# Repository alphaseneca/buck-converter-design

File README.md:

# buck-converter-design

This project focuses on the design and implementation of a **synchronous buck converter**, aiming for improved efficiency and reduced output ripple suitable for sensitive applications. The key aspect of the design is the careful selection of the **buck converter IC**, which plays a pivotal role in defining the overall performance, efficiency, and practicality of the system. Given the wide variety of ICs available, the process required in-depth research, tradeoff analysis, and simulation to select the most appropriate component.

## Introduction

A **buck converter** is a widely used DC-DC converter topology known for its simplicity and efficiency in stepping down voltage levels. However, the performance of a buck converter heavily depends on the **IC selected**, which determines parameters like efficiency, output ripple, switching frequency, and current handling capability.

In the early stages of this project, I explored various commercially available buck converter ICs. I started by reviewing the datasheet of the **LM2596-5V**, a commonly found and affordable buck converter IC used in general-purpose circuits. However, during the datasheet study, I realized that the LM2596 operates in **non-synchronous mode**, which uses an external diode in the freewheeling phase. This leads to higher losses, especially at lower output voltages or higher currents. And is also expensive.

Further research introduced me to the **synchronous buck converter topology**, where the freewheeling diode is replaced by a low-side MOSFET. This approach significantly improves efficiency by reducing diode losses, making it suitable for modern, high-performance applications where efficiency and thermal management are critical.

To assist in the selection process, I utilized **Texas Instruments' WEBENCH Designer**, an online tool that helps engineers simulate and optimize power supply designs based on their requirements. Using this tool, I evaluated various TI synchronous buck converter ICs, comparing parameters like efficiency, output current capability, switching frequency, and thermal performance.

## Theoretical Background

A **synchronous buck converter** is a type of step-down converter that replaces the freewheeling diode with a **low-side MOSFET**. It operates with two MOSFETs (high-side and low-side) and a PWM controller that ensures precise switching and dead-time management.

https://resources.pcb.cadence.com/blog/synchronous-vs-nonsynchronous-dc-dc-conversion

### How It Works:

- When the **high-side MOSFET** is ON, current flows from input → inductor → load → ground.
- When it's OFF, the **low-side MOSFET** turns ON and allows the inductor to continue supplying current (instead of using a diode).
- The **inductor** stores energy during the ON phase and releases it during the OFF phase, smoothing current.
- The **capacitor** filters voltage ripple and stabilizes output.

---

## Design Requirements

- Input Voltage Range: 10-14 VDC
- Output Voltage: 5V
- Output Continuous Current: 3A
- Switching Frequency: 600kHz
- Ripple Limits: \***\*2–3% of Vout i.e **0.02\*5 = 10mV\*\*
  [ Consumer / FCC Class B as per FCC Part 15 ]

### Components Selection

- Buck Converter IC:
  Used **TPS564257** because it supports a wide input range from 3V to 17V, which covers my system’s required 10V to 14V input. Its built-in enable threshold can be configured using external resistors to ensure the system only turns on when the input is above 10V, protecting against undervoltage. The converter also offers efficient performance at up to 4A output and includes safety features like overcurrent and thermal shutdown, making it a safe and compact solution for my power supply design.
- Inductor Value:
  Target inductor ripple current: **20% to 50% of output current (IOUT)**
  Use this to calculate **inductor value using the standard formula:**

$$
\Delta I_L = \frac{(V_{IN} - V_{OUT}) \times V_{OUT}}{V_{IN} \times L \times f_{SW}}
$$

$$
I_{L(PEAK)} = I_{OUT} + \frac{\Delta I_L}{2}
$$

And According to the datasheet the recommended Inductor Value is 4.7uH and calculating the current rating we came to know that the inductor should be able to handle around **4.2A.**

- Capacitor Value: The output capacitor value are also recommended in the datasheet as:
  $Cout$ ⇒ 44uF. And it should be able to handle the current as the following equation suggests and should have low ESR.
  And the input capacitor are $Cin$ = 10uF and an additional 100nF for high frequency filtering. And the Voltage rating should be greater than the Input Voltage range.

$$
I_{CO(RMS)} = \frac{V_{OUT} \times (V_{IN} - V_{OUT})}{\sqrt{12} \times V_{IN} \times L \times f_{SW}}
$$

### Output Voltage Calculation:

The output voltage is set by the help of voltage divider arrangement of the Rfbt and Rfbb resistors. The recommended Rfbt is 200kohm and Rfbb is 30kohm for setting the output to 5V. And for the voltage other than that we can set using this formula:

$$
V_{OUT} = 0.6V \times \left(1 + \frac{R_{FBT}}{R_{FBB}}\right)
$$

The datasheet recommends using 1% tolerance resistors and to improve efficiency at very light loads, consider using larger value resistors.

### UVLO (Under Voltage Lock Out)

The EN pin accepts the voltage from and using a series of resistors Rent and Renb the converter is only turned on when the input voltage is higher than 10V

**_Calculation for EN divider to turn ON at 10V:_**

$$
V_{EN} = V_{IN} \times \frac{RENB}{REN + RENB}
$$

$$
REN = RENB \times \left(\frac{V_{IN(ON)}}{V_{EN}} - 1\right)
$$

The $Ven$ is 1.19V and the $Renb$ should be in k ohm range and thus setting the $Renb$ ⇒ 30kohm will give $Ren$ ⇒ 210kohm.

### Reliability and Over Voltage Protection:

For adding the reliability of the buck converter and also to limit the upper voltage to around 14 V we added a TVS diode in parallel to to the input supply. The TVS diode is **PTVS12VZ1USK** to be exact.

### Circuit Design:

### PCB:

---

### Simulation:

Simulation of the circuit is done using **WEBENCH Power Designer**.

- [Startup Simulation](./Simulations/WBDesign_Startup-1.pdf)
- [Load Transient Simulation](./Simulations/WBDesign_Load%20Transient-2.pdf)
- [Input Transient Simulation](./Simulations/WBDesign_Input%20Transient-3.pdf)
- [Steady State Simulation](./Simulations/WBDesign_Steady%20State-4.pdf)

### References:

- [TI TPS564257 Buck Converter Datasheet](https://www.ti.com/lit/ds/symlink/tps564257.pdf)
- [WEBENCH Power Designer](https://webench.ti.com/power-designer/)

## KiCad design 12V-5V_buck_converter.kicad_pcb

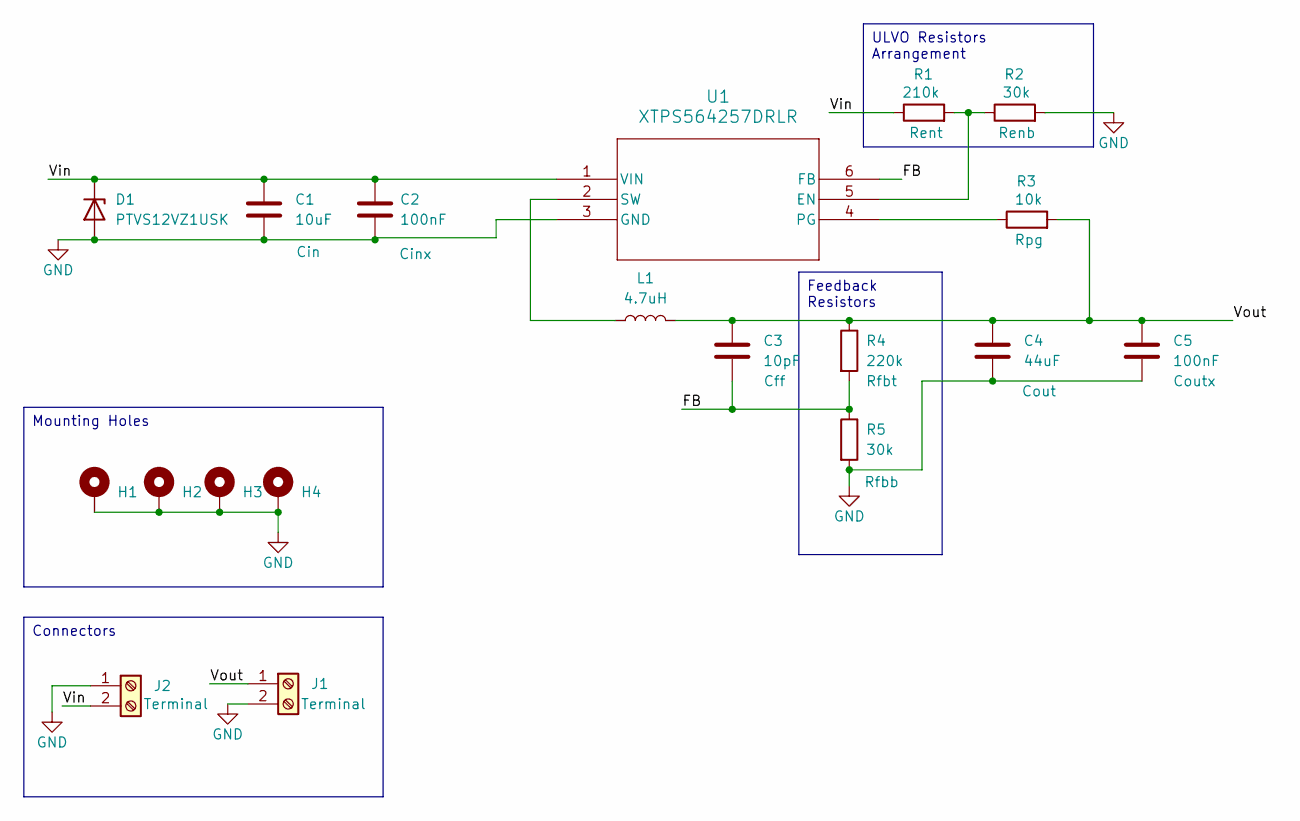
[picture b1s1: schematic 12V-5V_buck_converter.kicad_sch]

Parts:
C1: 10uF; C_0805_2012Metric
C2, C5: 100nF; C_0603_1608Metric
C3: 10pF; C_0402_1005Metric
C4: 44uF; C_0805_2012Metric
D1: PTVS12VZ1USK; Nexperia_DSN1608-2_1.6x0.8mm
H1, H2, H3, H4: MountingHole_Pad; MountingHole_2.2mm_M2_DIN965_Pad_TopBottom
J1, J2: Terminal; TerminalBlock_Phoenix_MPT-0,5-2-2.54_1x02_P2.54mm_Horizontal
L1: 4.7uH; IND_CLF10040T-4R7N-D
R1: 210k; R_0603_1608Metric
R2, R5: 30k; R_0603_1608Metric
R3: 10k; R_0603_1608Metric
R4: 220k; R_0603_1608Metric
U1: XTPS564257DRLR; TPS564242DRLR_TEX

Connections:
/FB: C3.2, R4.2, R5.1, U1.6 (FB)
/Vin: C1.1, C2.1, D1.1 (K), J2.2, R1.1, U1.1 (VIN)
/Vout: C3.1, C4.1, C5.1, J1.1, L1.2, R3.2, R4.1
GND: C1.2, C2.2, C4.2, C5.2, D1.2 (A), H1.1, H2.1, H3.1, H4.1, J1.2, J2.1, R2.2, R5.2, U1.3 (GND)
unnamed: R1.2, R2.1, U1.5 (EN)
unnamed: R3.1, U1.4 (PG)
unnamed: L1.1, U1.2 (SW)

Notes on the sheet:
Mounting Holes
Feedback Resistors
ULVO Resistors Arrangement
Connectors

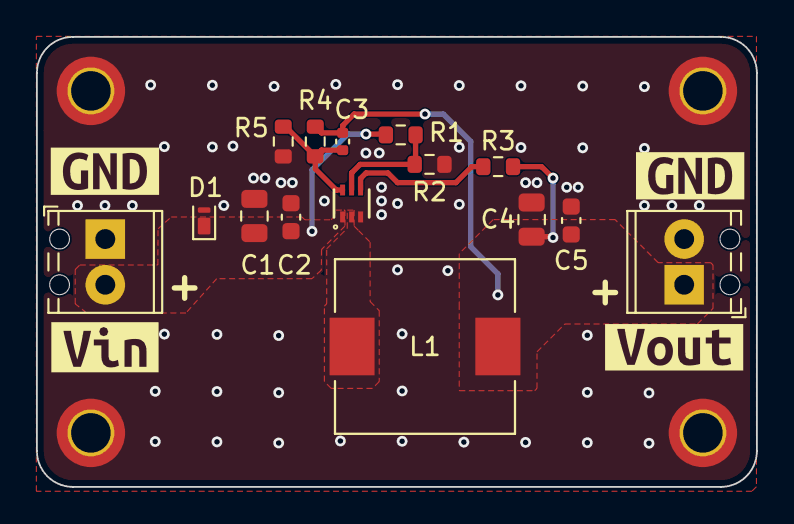
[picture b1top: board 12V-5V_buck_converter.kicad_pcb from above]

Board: 2 copper layers, 40.0 x 25.0 mm, 23 parts (0 on the bottom side), 7 nets.

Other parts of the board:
kibuzzard-6822FF75: G***; kibuzzard-6822FF75
kibuzzard-6822FFBE: G***; kibuzzard-6822FFBE
kibuzzard-68230884, kibuzzard-68230884#2: G***; kibuzzard-68230884

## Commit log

2025-05-13 added files
2025-05-13 corrected the formula tex
2026-06-02 chore: added workflow release file
2026-06-02 fix: changed for KICAD 10
